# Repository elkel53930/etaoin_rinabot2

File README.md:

# 璃奈ちゃんbot TYPE2

このリポジトリは、同人誌「璃奈ちゃんを作ろう！TYPE2」の参考資料を公開するものです。

## ディレクトリ構成

```
etaoin_rinabot2
├── app : 主にPythonスクリプト
│   ├── board : 璃奈ちゃんboard
│   ├── drive : 璃奈ちゃんdrive
│   ├── etc : その他スクリプト
│   ├── frame : 璃奈ちゃんframe
│   ├── rinabot : 高レベルスクリプトやシナリオ実行スクリプト
│   ├── scenario : サンプルシナリオファイル
│   ├── slide : スライドショー機能
│   └── speech : 璃奈ちゃんspeech
├── elec : 各プリント基板のKiCadデータ
│   ├── board : 璃奈ちゃんboard制御基板
│   ├── hub : ハブ基板
│   ├── led_a : LEDのモジュール
│   └── motor_driver : 璃奈ちゃんdrive制御基板
└── fsw : ファームウェア
　   ├── board : 璃奈ちゃんboard
　   └── drive : 璃奈ちゃんdrive
```

## 3DCADデータ

3DCADデータは以下のURLで公開しています。
Google Chromeでは表示できないことがあるようです。
Microsoft Edgeで閲覧可能であることを確認しています。

https://a360.co/4q07Nhn

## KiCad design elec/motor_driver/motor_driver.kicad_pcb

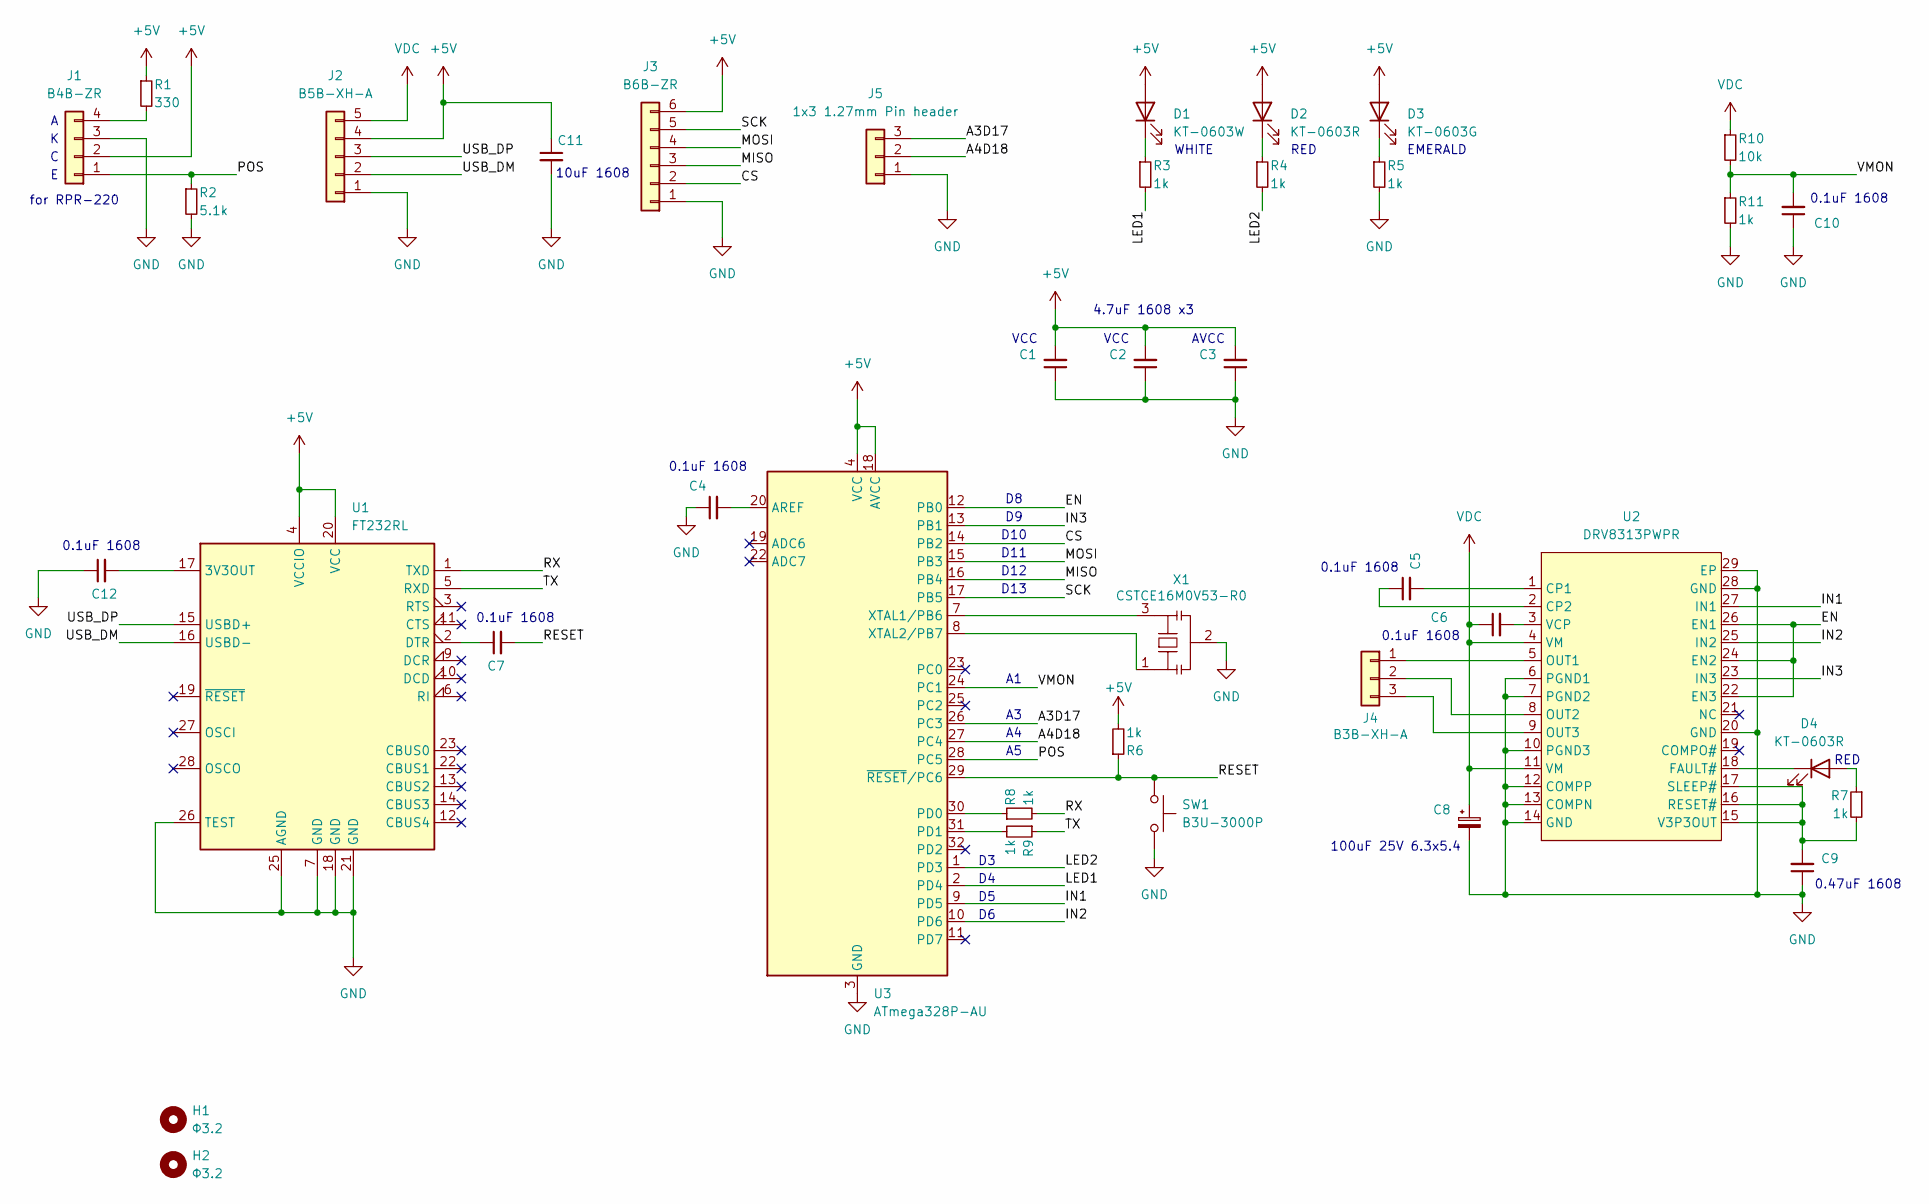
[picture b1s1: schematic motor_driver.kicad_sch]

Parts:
C1, C2, C3: CL10A475KO8NNNC; C_0603_1608Metric
C4, C5, C6, C7, C10, C12: CC0603KRX7R9BB104; C_0603_1608Metric
C8: RST100UF25V004; CP_Elec_6.3x5.4
C9: CL10B474KA8NNNC; C_0603_1608Metric
C11: CL10A106KP8NNNC; C_0603_1608Metric
D1: KT-0603W; LED_0603_1608Metric
D2, D4: KT-0603R; LED_0603_1608Metric
D3: KT-0603G; LED_0603_1608Metric
H1, H2: Φ3.2; MountingHole_3.2mm_M3
J1: B4B-ZR; JST_ZH_B4B-ZR_1x04_P1.50mm_Vertical
J2: B5B-XH-A; JST_XH_B5B-XH-A_1x05_P2.50mm_Vertical
J3: B6B-ZR; JST_ZH_B6B-ZR_1x06_P1.50mm_Vertical
J4: B3B-XH-A; JST_XH_B3B-XH-A_1x03_P2.50mm_Vertical
J5: 1x3 1.27mm Pin header; PinHeader_1x03_P1.27mm_Vertical
R1: 330; R_0603_1608Metric
R2: 5.1k; R_0603_1608Metric
R3, R4, R5, R6, R7, R8, R9, R11: 1k; R_0603_1608Metric
R10: 10k; R_0603_1608Metric
SW1: B3U-3000P; SW_SPST_B3U-3000P-B
U1: FT232RL; SSOP-28_5.3x10.2mm_P0.65mm
U2: DRV8313PWPR; HTSSOP-28-1EP_4.4x9.7mm_P0.65mm_EP2.75x6.2mm_ThermalVias
U3: ATmega328P-AU; TQFP-32_7x7mm_P0.8mm
X1: CSTCE16M0V53-R0; CSTCE

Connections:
+5V: C1.2, C2.2, C3.2, C11.1, D1.2 (A), D2.2 (A), D3.2 (A), J1.2, J2.4, J3.6, R1.1, R6.2, U1.4 (VCCIO), U1.20 (VCC), U3.4 (VCC), U3.6 (VCC), U3.18 (AVCC)
/A3D17: J5.3, U3.26 (PC3)
/A4D18: J5.2, U3.27 (PC4)
/CS: J3.2, U3.14 (PB2)
/EN: U2.22 (EN3), U2.24 (EN2), U2.26 (EN1), U3.12 (PB0)
/IN1: U2.27 (IN1), U3.9 (PD5)
/IN2: U2.25 (IN2), U3.10 (PD6)
/IN3: U2.23 (IN3), U3.13 (PB1)
/LED1: R3.2, U3.2 (PD4)
/LED2: R4.2, U3.1 (PD3)
/MISO: J3.3, U3.16 (PB4)
/MOSI: J3.4, U3.15 (PB3)
/POS: J1.1, R2.1, U3.28 (PC5)
/RESET: C7.2, R6.1, SW1.1, U3.29 (~RESET/PC6)
/RX: R8.2, U1.1 (TXD)
/SCK: J3.5, U3.17 (PB5)
/TX: R9.1, U1.5 (RXD)
/USB_DM: J2.2, U1.16 (USBD-)
/USB_DP: J2.3, U1.15 (USBD+)
/VMON: C10.2, R10.2, R11.1, U3.24 (PC1)
GND: C1.1, C2.1, C3.1, C4.1, C8.2, C9.1, C10.1, C11.2, C12.1, J1.3, J2.1, J3.1, J5.1, R2.2, R5.2, R11.2, SW1.2, U1.7 (GND), U1.18 (GND), U1.21 (GND), U1.25 (AGND), U1.26 (TEST), U2.6 (PGND1), U2.7 (PGND2), U2.10 (PGND3), U2.12 (COMPP), U2.13 (COMPN), U2.14 (GND), U2.20 (GND), U2.28 (GND), U2.29 (EP), U3.3 (GND), U3.5 (GND), U3.21 (GND), X1.2
unnamed: D1.1 (K), R3.1
unnamed: D2.1 (K), R4.1
unnamed: D3.1 (K), R5.1
unnamed: D4.2 (A), R7.1
unnamed: D4.1 (K), U2.18 (FAULT#)
unnamed: J1.4, R1.2
unnamed: J4.1, U2.5 (OUT1)
unnamed: J4.2, U2.8 (OUT2)
unnamed: J4.3, U2.9 (OUT3)
unnamed: C12.2, U1.17 (3V3OUT)
unnamed: C7.1, U1.2 (DTR)
unnamed: C5.2, U2.1 (CP1)
unnamed: C5.1, U2.2 (CP2)
unnamed: C9.2, R7.2, U2.15 (V3P3OUT), U2.16 (RESET#), U2.17 (SLEEP#)
unnamed: C6.2, U2.3 (VCP)
unnamed: C4.2, U3.20 (AREF)
unnamed: R8.1, U3.30 (PD0)
unnamed: R9.2, U3.31 (PD1)
unnamed: U3.7 (XTAL1/PB6), X1.3
unnamed: U3.8 (XTAL2/PB7), X1.1
VDC: C6.1, C8.1, J2.5, R10.1, U2.4 (VM), U2.11 (VM)

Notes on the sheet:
D12
VCC
RED
D10
EMERALD
0.1uF 1608
WHITE
100uF 25V 6.3x5.4
10uF 1608
AVCC
for RPR-220
0.47uF 1608
4.7uF 1608 x3
D13
D11

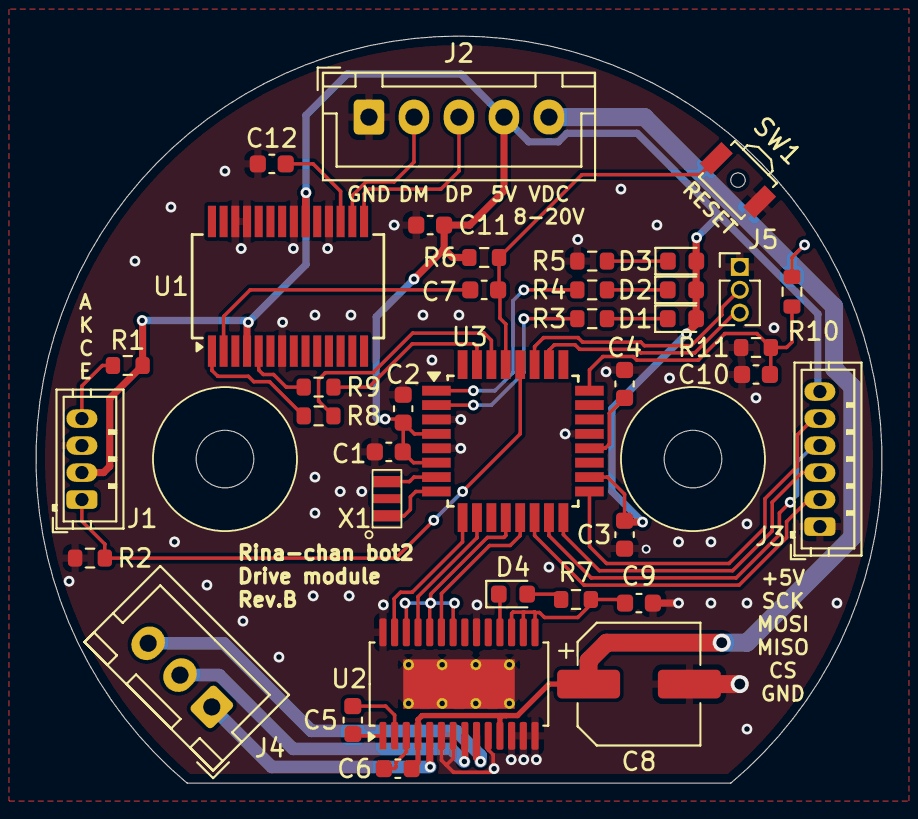
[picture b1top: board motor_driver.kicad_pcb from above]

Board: 2 copper layers, 47.0 x 41.5 mm, 39 parts (0 on the bottom side), 42 nets.

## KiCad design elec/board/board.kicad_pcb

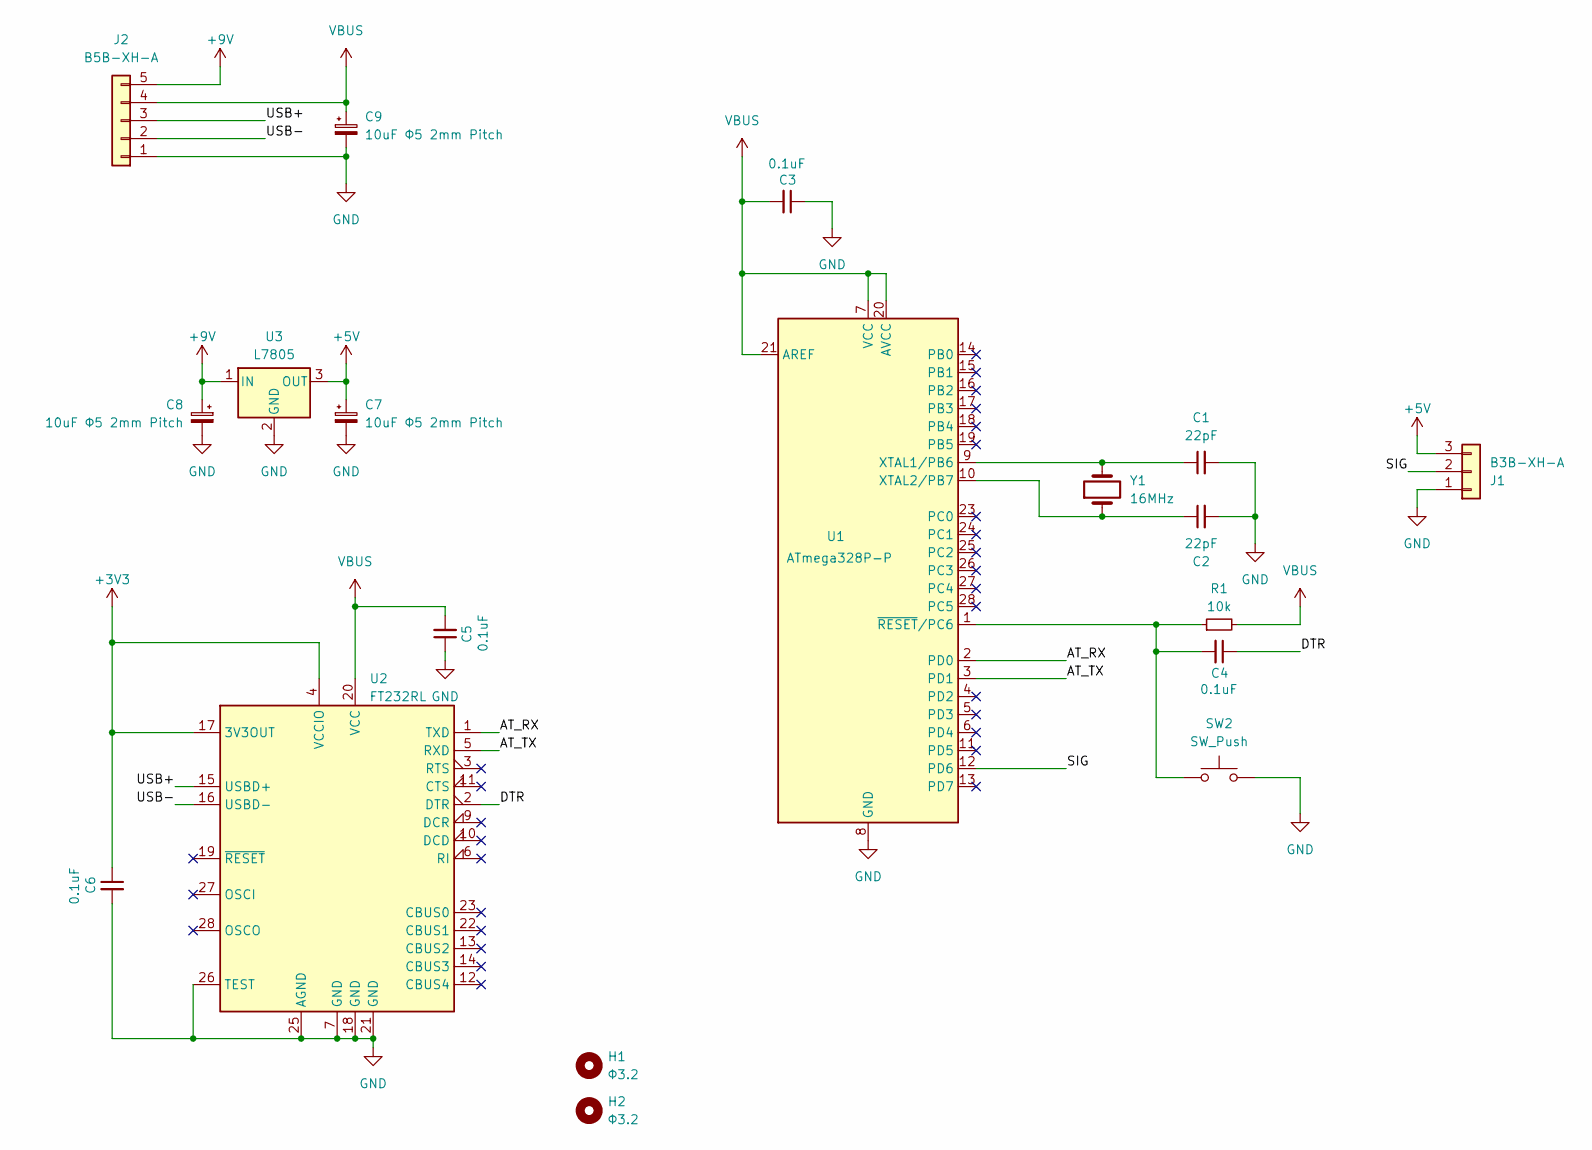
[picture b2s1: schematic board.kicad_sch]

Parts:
C1, C2: 22pF; C_Disc_D5.1mm_W3.2mm_P5.00mm
C3, C4, C5, C6: 0.1uF; C_Disc_D5.1mm_W3.2mm_P5.00mm
C7, C8, C9: 10uF Φ5 2mm Pitch; CP_Radial_D5.0mm_P2.00mm
H1, H2: Φ3.2; MountingHole_3.2mm_M3
J1: B3B-XH-A; JST_XH_B3B-XH-A_1x03_P2.50mm_Vertical
J2: B5B-XH-A; JST_XH_B5B-XH-A_1x05_P2.50mm_Vertical
R1: 10k; R_Axial_DIN0207_L6.3mm_D2.5mm_P7.62mm_Horizontal
SW2: SW_Push; SW_PUSH_6mm
U1: ATmega328P-P; DIP-28_W7.62mm
U2: FT232RL; SSOP-28_5.3x10.2mm_P0.65mm
U3: L7805; TO-220F-3_Vertical
Y1: 16MHz; Crystal_HC49-4H_Vertical

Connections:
+3V3: C6.1, U2.4 (VCCIO), U2.17 (3V3OUT)
+5V: C7.1, J1.3, U3.3 (OUT)
+9V: C8.1, J2.5, U3.1 (IN)
/AT_RX: U1.2 (PD0), U2.1 (TXD)
/AT_TX: U1.3 (PD1), U2.5 (RXD)
/DTR: C4.1, U2.2 (DTR)
/SIG: J1.2, U1.12 (PD6)
/USB+: J2.3, U2.15 (USBD+)
/USB-: J2.2, U2.16 (USBD-)
GND: C1.2, C2.2, C3.1, C5.1, C6.2, C7.2, C8.2, C9.2, J1.1, J2.1, SW2.2, U1.8 (GND), U1.22 (GND), U2.7 (GND), U2.18 (GND), U2.21 (GND), U2.25 (AGND), U2.26 (TEST), U3.2 (GND)
unnamed: C1.1, U1.9 (XTAL1/PB6), Y1.2
unnamed: C2.1, U1.10 (XTAL2/PB7), Y1.1
unnamed: C4.2, R1.1, SW2.1, U1.1 (~RESET/PC6)
VBUS: C3.2, C5.2, C9.1, J2.4, R1.2, U1.7 (VCC), U1.20 (AVCC), U1.21 (AREF), U2.20 (VCC)

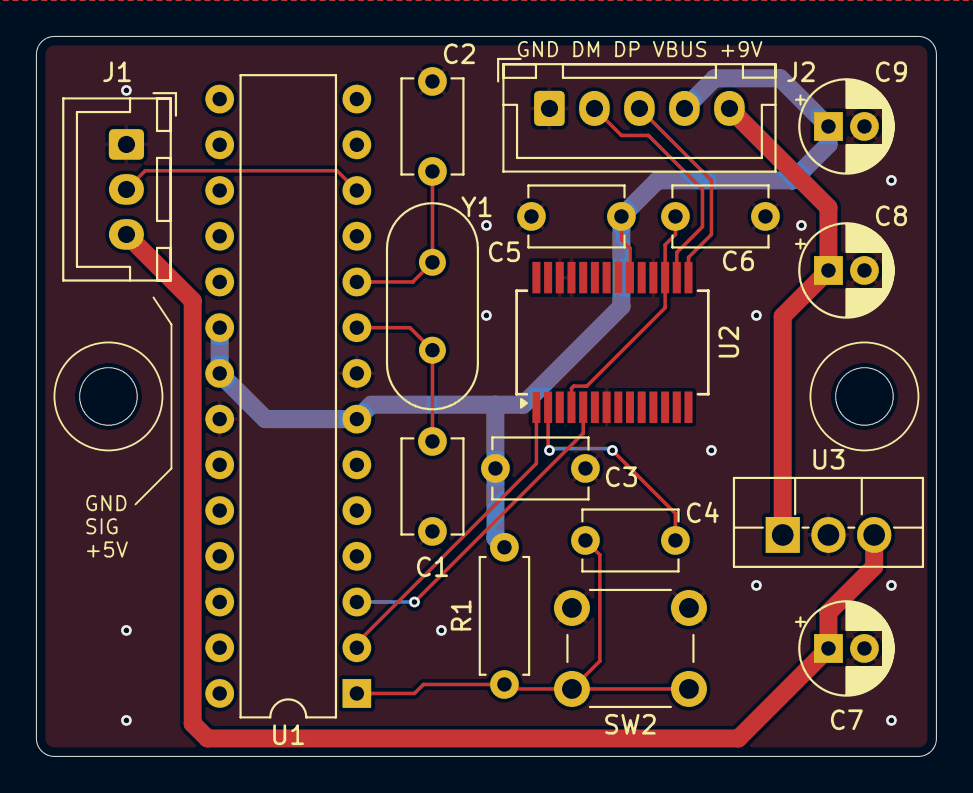
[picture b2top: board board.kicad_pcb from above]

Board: 2 copper layers, 50.0 x 40.0 mm, 19 parts (0 on the bottom side), 14 nets.

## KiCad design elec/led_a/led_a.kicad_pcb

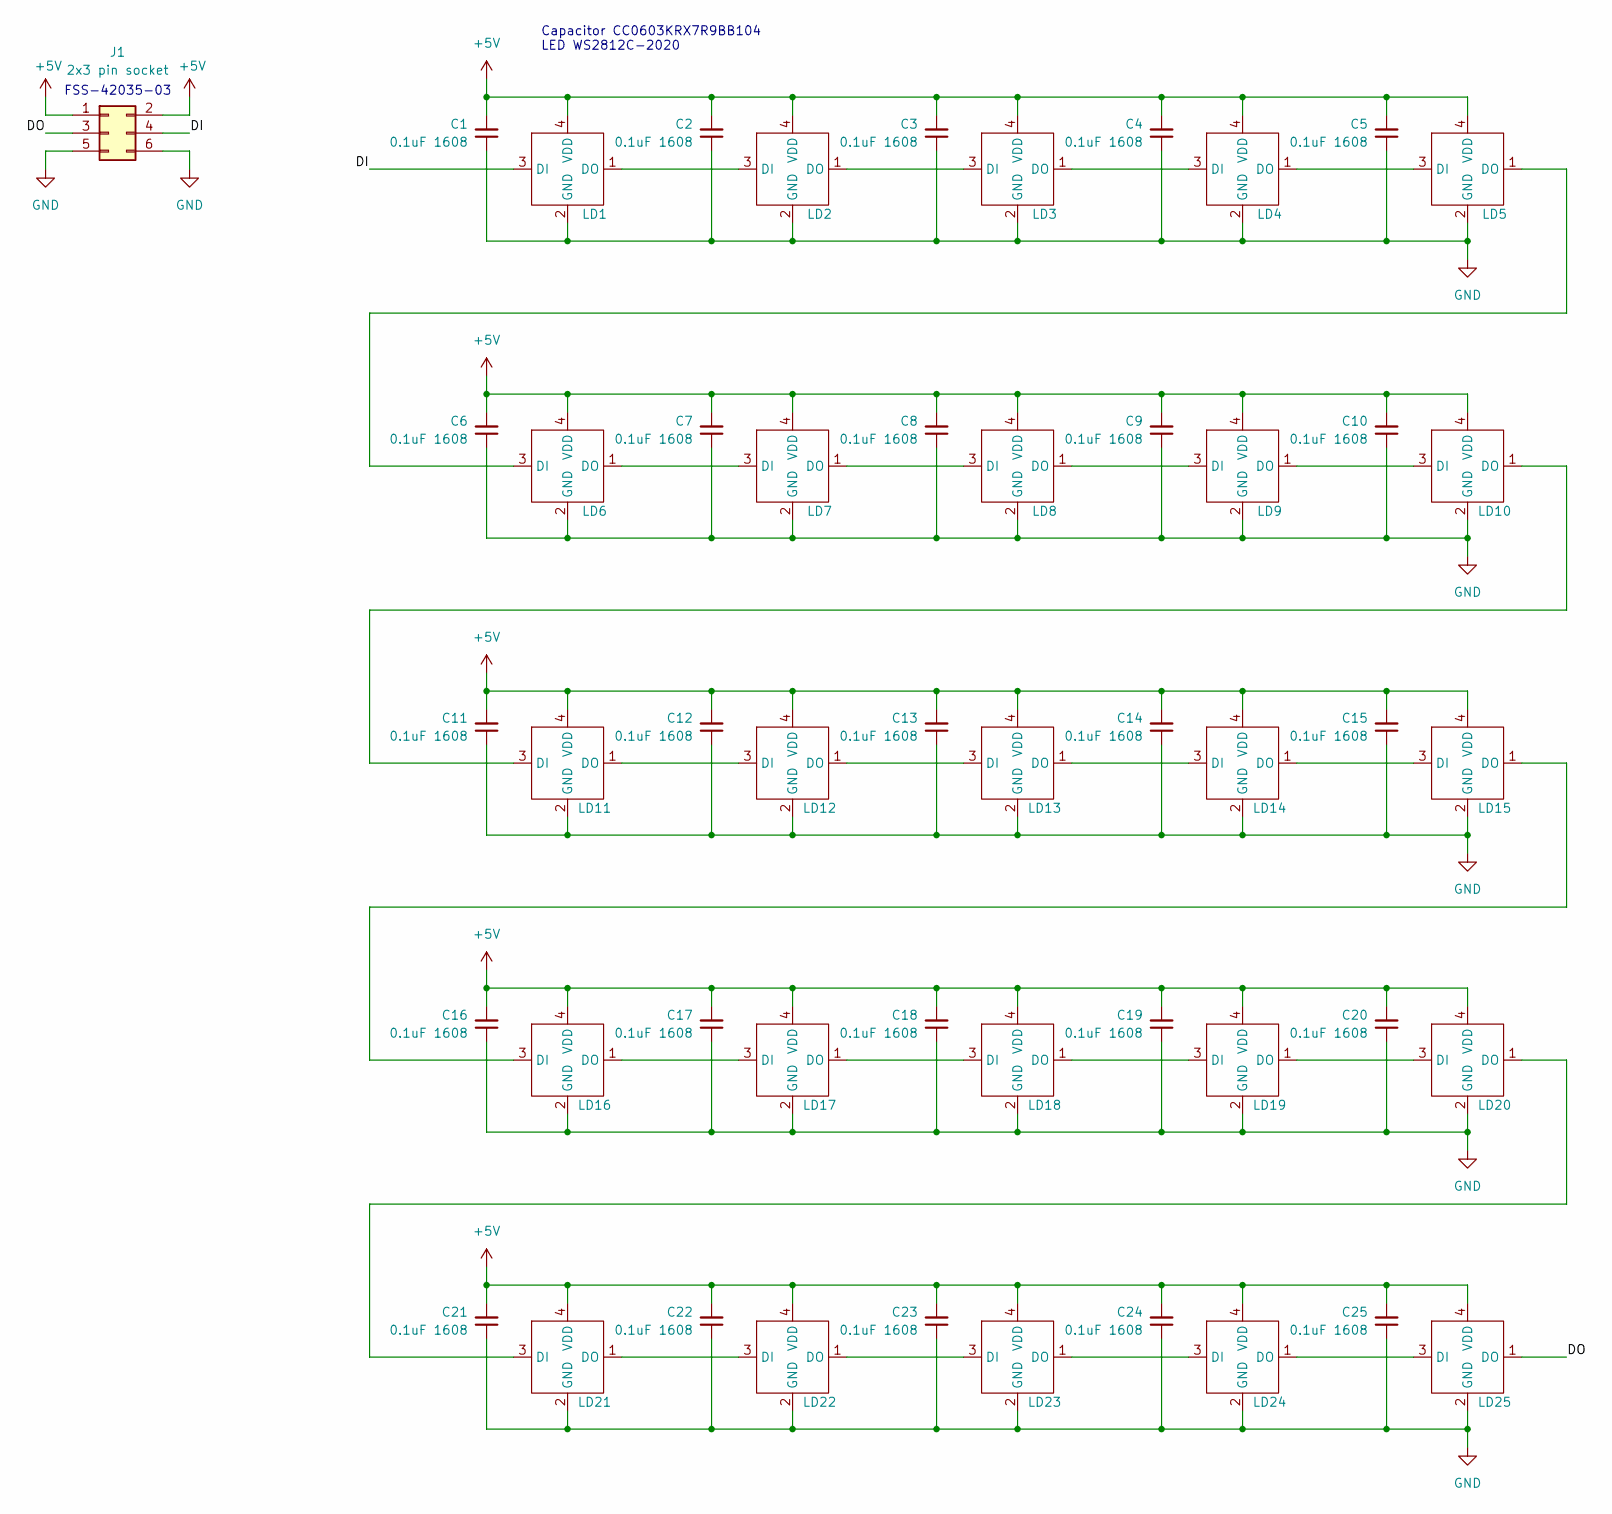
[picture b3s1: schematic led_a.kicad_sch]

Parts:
C1, C2, C3, C4, C5, C6, C7, C8, C9, C10, C11, C12, C13, C14, C15, C16, C17, C18, C19, C20, C21, C22, C23, C24, C25: 0.1uF 1608; C_0603_1608Metric
J1: 2x3 pin socket; PinHeader_2x03_P2.54mm_Vertical
LD1, LD2, LD3, LD4, LD5, LD6, LD7, LD8, LD9, LD10, LD11, LD12, LD13, LD14, LD15, LD16, LD17, LD18, LD19, LD20, LD21, LD22, LD23, LD24, LD25: LED_WS2812B-2020_PLCC4_2.0x2.0mm

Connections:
+5V: C1.2, C2.2, C3.2, C4.2, C5.2, C6.2, C7.2, C8.2, C9.2, C10.2, C11.2, C12.2, C13.2, C14.2, C15.2, C16.2, C17.2, C18.2, C19.2, C20.2, C21.2, C22.2, C23.2, C24.2, C25.2, J1.1, J1.2, LD1.4 (VDD), LD2.4 (VDD), LD3.4 (VDD), LD4.4 (VDD), LD5.4 (VDD), LD6.4 (VDD), LD7.4 (VDD), LD8.4 (VDD), LD9.4 (VDD), LD10.4 (VDD), LD11.4 (VDD), LD12.4 (VDD), LD13.4 (VDD), LD14.4 (VDD), LD15.4 (VDD), LD16.4 (VDD), LD17.4 (VDD), LD18.4 (VDD), LD19.4 (VDD), LD20.4 (VDD), LD21.4 (VDD), LD22.4 (VDD), LD23.4 (VDD), LD24.4 (VDD), LD25.4 (VDD)
/DI: J1.4, LD1.3 (DI)
/DO: J1.3, LD25.1 (DO)
GND: C1.1, C2.1, C3.1, C4.1, C5.1, C6.1, C7.1, C8.1, C9.1, C10.1, C11.1, C12.1, C13.1, C14.1, C15.1, C16.1, C17.1, C18.1, C19.1, C20.1, C21.1, C22.1, C23.1, C24.1, C25.1, J1.5, J1.6, LD1.2 (GND), LD2.2 (GND), LD3.2 (GND), LD4.2 (GND), LD5.2 (GND), LD6.2 (GND), LD7.2 (GND), LD8.2 (GND), LD9.2 (GND), LD10.2 (GND), LD11.2 (GND), LD12.2 (GND), LD13.2 (GND), LD14.2 (GND), LD15.2 (GND), LD16.2 (GND), LD17.2 (GND), LD18.2 (GND), LD19.2 (GND), LD20.2 (GND), LD21.2 (GND), LD22.2 (GND), LD23.2 (GND), LD24.2 (GND), LD25.2 (GND)
unnamed: LD1.1 (DO), LD2.3 (DI)
unnamed: LD2.1 (DO), LD3.3 (DI)
unnamed: LD3.1 (DO), LD4.3 (DI)
unnamed: LD4.1 (DO), LD5.3 (DI)
unnamed: LD5.1 (DO), LD6.3 (DI)
unnamed: LD6.1 (DO), LD7.3 (DI)
unnamed: LD7.1 (DO), LD8.3 (DI)
unnamed: LD8.1 (DO), LD9.3 (DI)
unnamed: LD9.1 (DO), LD10.3 (DI)
unnamed: LD10.1 (DO), LD11.3 (DI)
unnamed: LD11.1 (DO), LD12.3 (DI)
unnamed: LD12.1 (DO), LD13.3 (DI)
unnamed: LD13.1 (DO), LD14.3 (DI)
unnamed: LD14.1 (DO), LD15.3 (DI)
unnamed: LD15.1 (DO), LD16.3 (DI)
unnamed: LD16.1 (DO), LD17.3 (DI)
unnamed: LD17.1 (DO), LD18.3 (DI)
unnamed: LD18.1 (DO), LD19.3 (DI)
unnamed: LD19.1 (DO), LD20.3 (DI)
unnamed: LD20.1 (DO), LD21.3 (DI)
unnamed: LD21.1 (DO), LD22.3 (DI)
unnamed: LD22.1 (DO), LD23.3 (DI)
unnamed: LD23.1 (DO), LD24.3 (DI)
unnamed: LD24.1 (DO), LD25.3 (DI)

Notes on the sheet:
Capacitor CC0603KRX7R9BB104 LED WS2812C-2020
FSS-42035-03

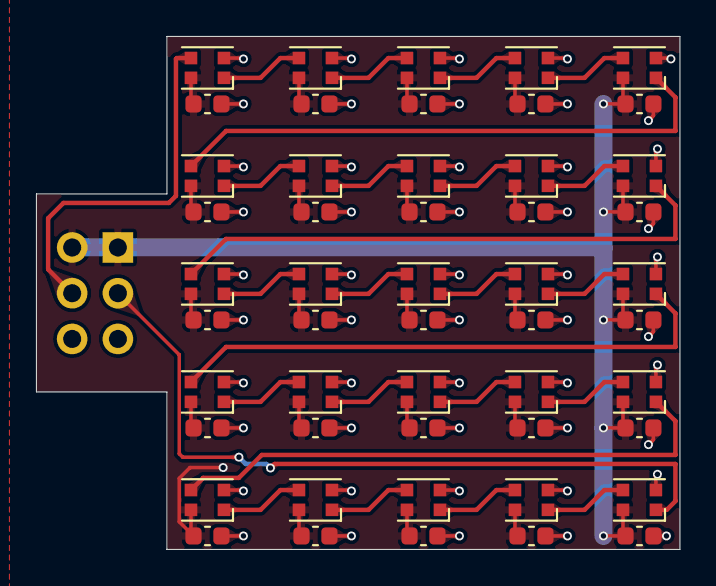
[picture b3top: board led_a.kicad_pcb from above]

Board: 2 copper layers, 35.8 x 28.5 mm, 51 parts (1 on the bottom side), 28 nets.

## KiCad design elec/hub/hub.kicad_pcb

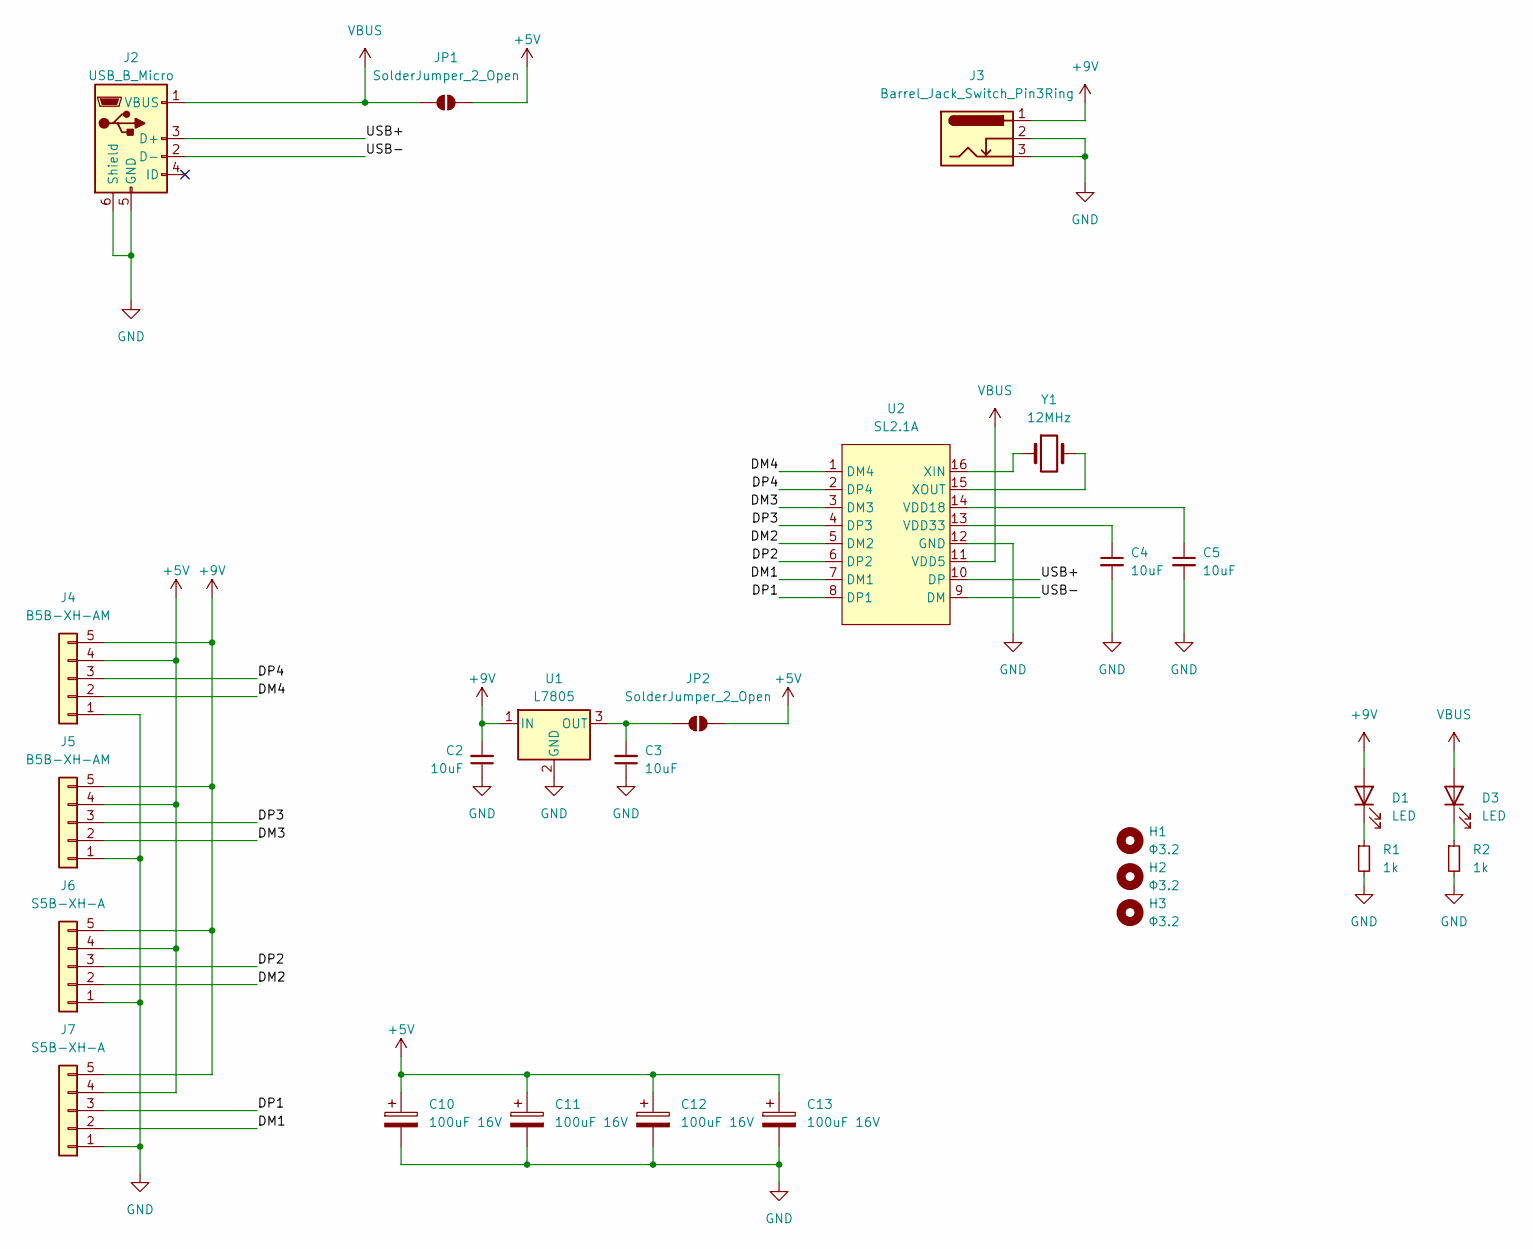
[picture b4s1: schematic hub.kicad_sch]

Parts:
C2, C3, C4, C5: 10uF; C_0805_2012Metric
C10, C11, C12, C13: 100uF 16V; CP_Elec_6.3x5.4
D1, D3: LED; LED_0603_1608Metric
H1, H2, H3: Φ3.2; MountingHole_3.2mm_M3
J2: USB_B_Micro; USB_Micro-B_Molex-105017-0001
J3: Barrel_Jack_Switch_Pin3Ring; PJ-002A
J4, J5: B5B-XH-AM; JST_XH_B5B-XH-AM_1x05_P2.50mm_Vertical
J6, J7: S5B-XH-A; JST_XH_S5B-XH-A_1x05_P2.50mm_Horizontal
JP1, JP2: SolderJumper_2_Open; SolderJumper-2_P1.3mm_Open_Pad1.0x1.5mm
R1, R2: 1k; R_0603_1608Metric
U1: L7805; TO-252-2
U2: SL2.1A; SOP-16_3.9x9.9mm_P1.27mm
Y1: 12MHz; Crystal_HC49-4H_Vertical

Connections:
+5V: C10.1, C11.1, C12.1, C13.1, J4.4, J5.4, J6.4, J7.4, JP1.1 (A), JP2.1 (A)
+9V: C2.2, D1.2 (A), J3.1, J4.5, J5.5, J6.5, J7.5, U1.1 (IN)
/DM1: J7.2, U2.7 (DM1)
/DM2: J6.2, U2.5 (DM2)
/DM3: J5.2, U2.3 (DM3)
/DM4: J4.2, U2.1 (DM4)
/DP1: J7.3, U2.8 (DP1)
/DP2: J6.3, U2.6 (DP2)
/DP3: J5.3, U2.4 (DP3)
/DP4: J4.3, U2.2 (DP4)
/USB+: J2.3 (D+), U2.10 (DP); also elsewhere on the board
/USB-: J2.2 (D-), U2.9 (DM); also elsewhere on the board
GND: C2.1, C3.1, C4.2, C5.2, C10.2, C11.2, C12.2, C13.2, J2.5 (GND), J2.6 (Shield), J3.2, J3.3, J4.1, J5.1, J6.1, J7.1, R1.2, R2.2, U1.2 (GND), U2.12 (GND); also elsewhere on the board
unnamed: D1.1 (K), R1.1
unnamed: D3.1 (K), R2.1
unnamed: C3.2, JP2.2 (B), U1.3 (OUT)
unnamed: C5.1, U2.14 (VDD18)
unnamed: C4.1, U2.13 (VDD33)
unnamed: U2.16 (XIN), Y1.1
unnamed: U2.15 (XOUT), Y1.2
VBUS: D3.2 (A), J2.1 (VBUS), JP1.2 (B), U2.11 (VDD5); also elsewhere on the board

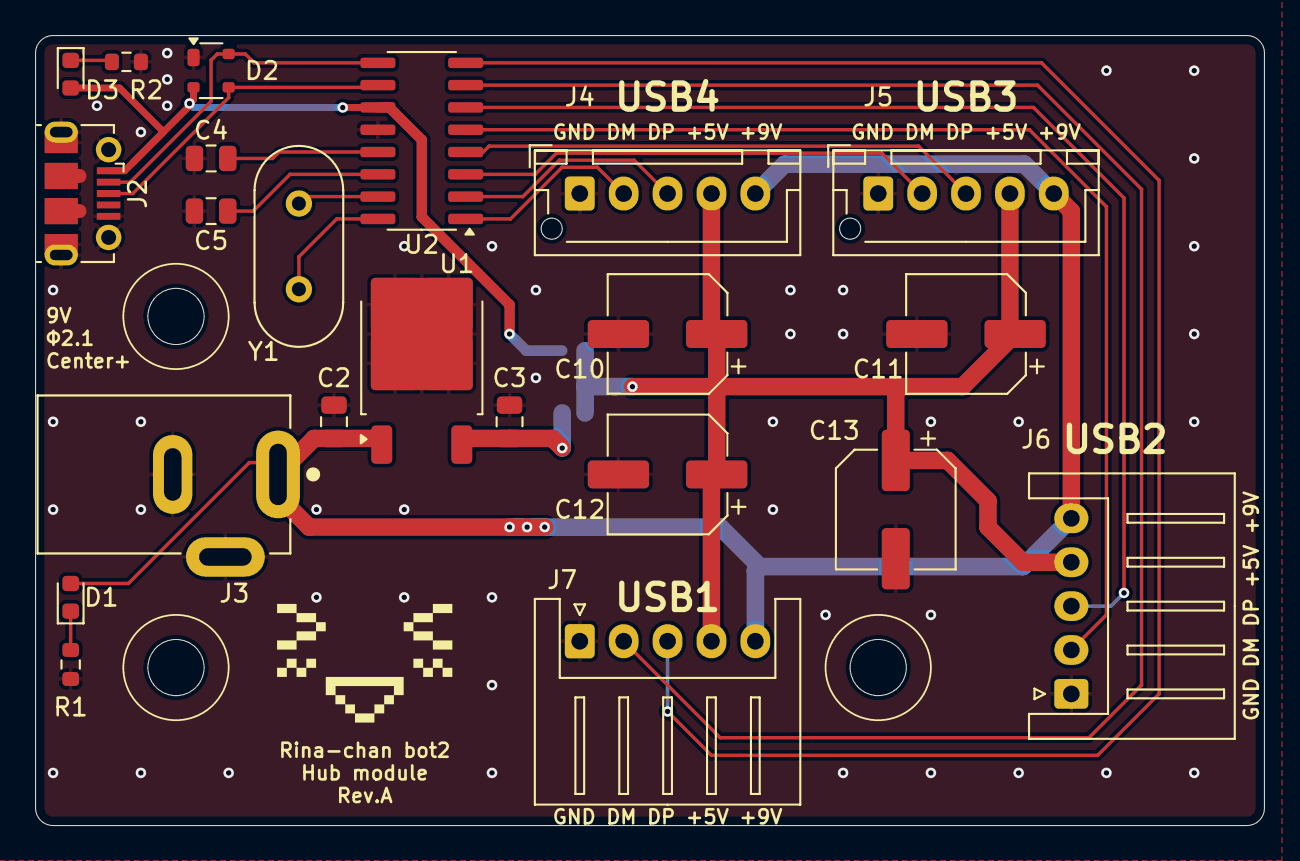
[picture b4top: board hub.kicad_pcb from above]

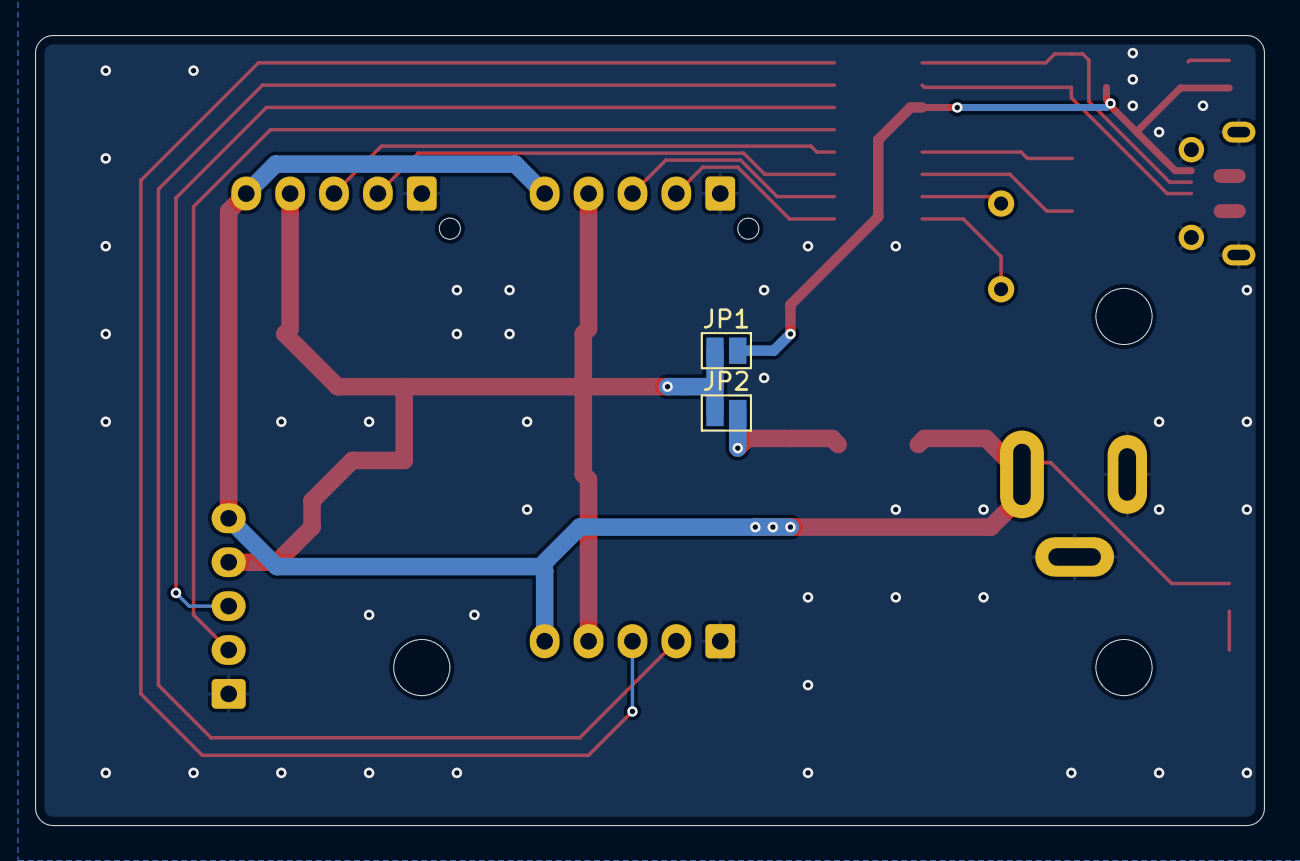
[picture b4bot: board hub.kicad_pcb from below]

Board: 2 copper layers, 70.0 x 45.0 mm, 27 parts (2 on the bottom side), 21 nets.

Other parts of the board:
D2: SP0503BAHT; SOT-143

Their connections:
/USB+: D2.3 (K); also elsewhere on the board
/USB-: D2.4 (K); also elsewhere on the board
GND: D2.1 (A); also elsewhere on the board
VBUS: D2.2 (K); also elsewhere on the board

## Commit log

2025-06-12 Add front cover image
2025-06-12 Upload files
2025-10-08 Update URL
